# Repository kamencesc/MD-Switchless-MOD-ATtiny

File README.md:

# UNTESTED
Note: After programming the Attiny, the RST pin is used as a in/out pin, so you need to make (or buy) a High Voltage Programmer to fuse-reset as you can see there: (https://sites.google.com/site/wayneholder/attiny-fuse-reset)

# MD Switchless MOD ATtiny
Sega Mega Drive/Genesis Switchless mod with an ATtiny85

Similar to the Switchless Mod code for Sega Saturn (https://github.com/sebknzl/saturnmod), this code is writed from zero and works this way:

- It change between 3 regions, 1 = PAL (Default at first time that the code runs and you can change it if you wish), 2 = USA, 3 = JAPAN
- Short press of  the reset button does the region change (EU->USA->JAP->EU....)
- The region is saved to the internat EEPROM for the next boot
- Long press of the reset button (+2 seconds) does the reset

Code was typed in the Adrduino IDE, you can find the pins config on the source code.

There's an untested PCB desing for and easy installation, maybe it doesn't fit on all revision boards.

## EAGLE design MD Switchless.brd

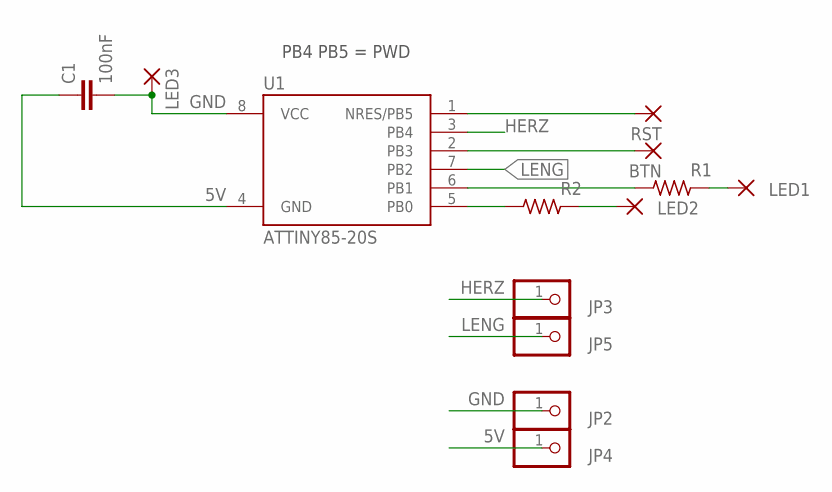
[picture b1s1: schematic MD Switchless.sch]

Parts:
BTN: WIREPADSMD1,27-254; SMD1,27-2,54
C1: 100nF; 0805
JP2, JP3, JP4, JP5: PINHD-1X1; 1X01
LED1, LED2, LED3: WIREPADSMD1,27-254; SMD1,27-2,54
R1, R2: R_0805; R0805
RST: WIREPADSMD1,27-254; SMD1,27-2,54
U1: ATTINY85-20S; SOIC8_EIAJ_208MIL

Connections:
5V: C1.1, JP4.1, U1.4 (GND)
BTN: BTN.1, U1.2 (PB3)
GND: C1.2, JP2.1, LED3.1, U1.8 (VCC)
HERZ: JP3.1, U1.3 (PB4)
L1: LED1.1, R1.2
L2: LED2.1, R2.2
LENG: JP5.1, U1.7 (PB2)
RL1: R1.1, U1.6 (PB1)
RL2: R2.1, U1.5 (PB0)
RST: RST.1, U1.1 (NRES/PB5)

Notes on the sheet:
PB4 PB5 = PWD

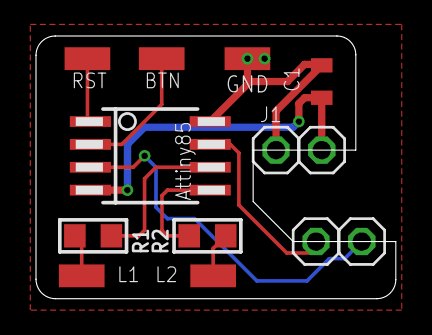
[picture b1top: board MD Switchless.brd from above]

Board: 2 copper layers, 20.0 x 14.6 mm, 13 parts (0 on the bottom side), 10 nets.

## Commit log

2019-07-24 Code
    Code typed in Arduino IDE
2019-07-24 Add files via upload
    PCB size and traces width
2019-07-24 Add files via upload
    minor changes
2019-07-25 Add files via upload
    Wrong position on headers, now it fits perfect
2019-07-25 Add files via upload
    ATtiny85 label on the wrong side
2019-08-01 Add files via upload
    Minor changes, R1-3 now are 220ohm
2020-11-16 Add files via upload
    Update a config const for a anode/catode LED
2022-02-19 Add files via upload
    traces and pinout changes
2022-02-19 Add files via upload
    Code revision, change pinouts after PCB revision
2022-02-19 Add files via upload
    PCB render
2022-02-19 Add files via upload
    header

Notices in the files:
parts and their libraries:
SparkFun-Capacitors: Licensing: Creative Commons ShareAlike 4.0 International - https://creativecommons.org/licenses/by-sa/4.0
rc-master-smd: Copyright (C) 2007, Bob Starr
